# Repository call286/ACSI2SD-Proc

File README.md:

# ACSI2SD-Proc
version for QFP100 controller
ACSI0123_512M.xml contains default configuration for scsi2sd-util

# Hardware - finally with placement help and board layout

- Board layout isn't the original layout, it's just for helping with rough position of parts
- DRC/ERC passing
- interactive BOM in kicad folder

Board Render Front           |  Board Render Back
:-------------------------:|:-------------------------:
 |

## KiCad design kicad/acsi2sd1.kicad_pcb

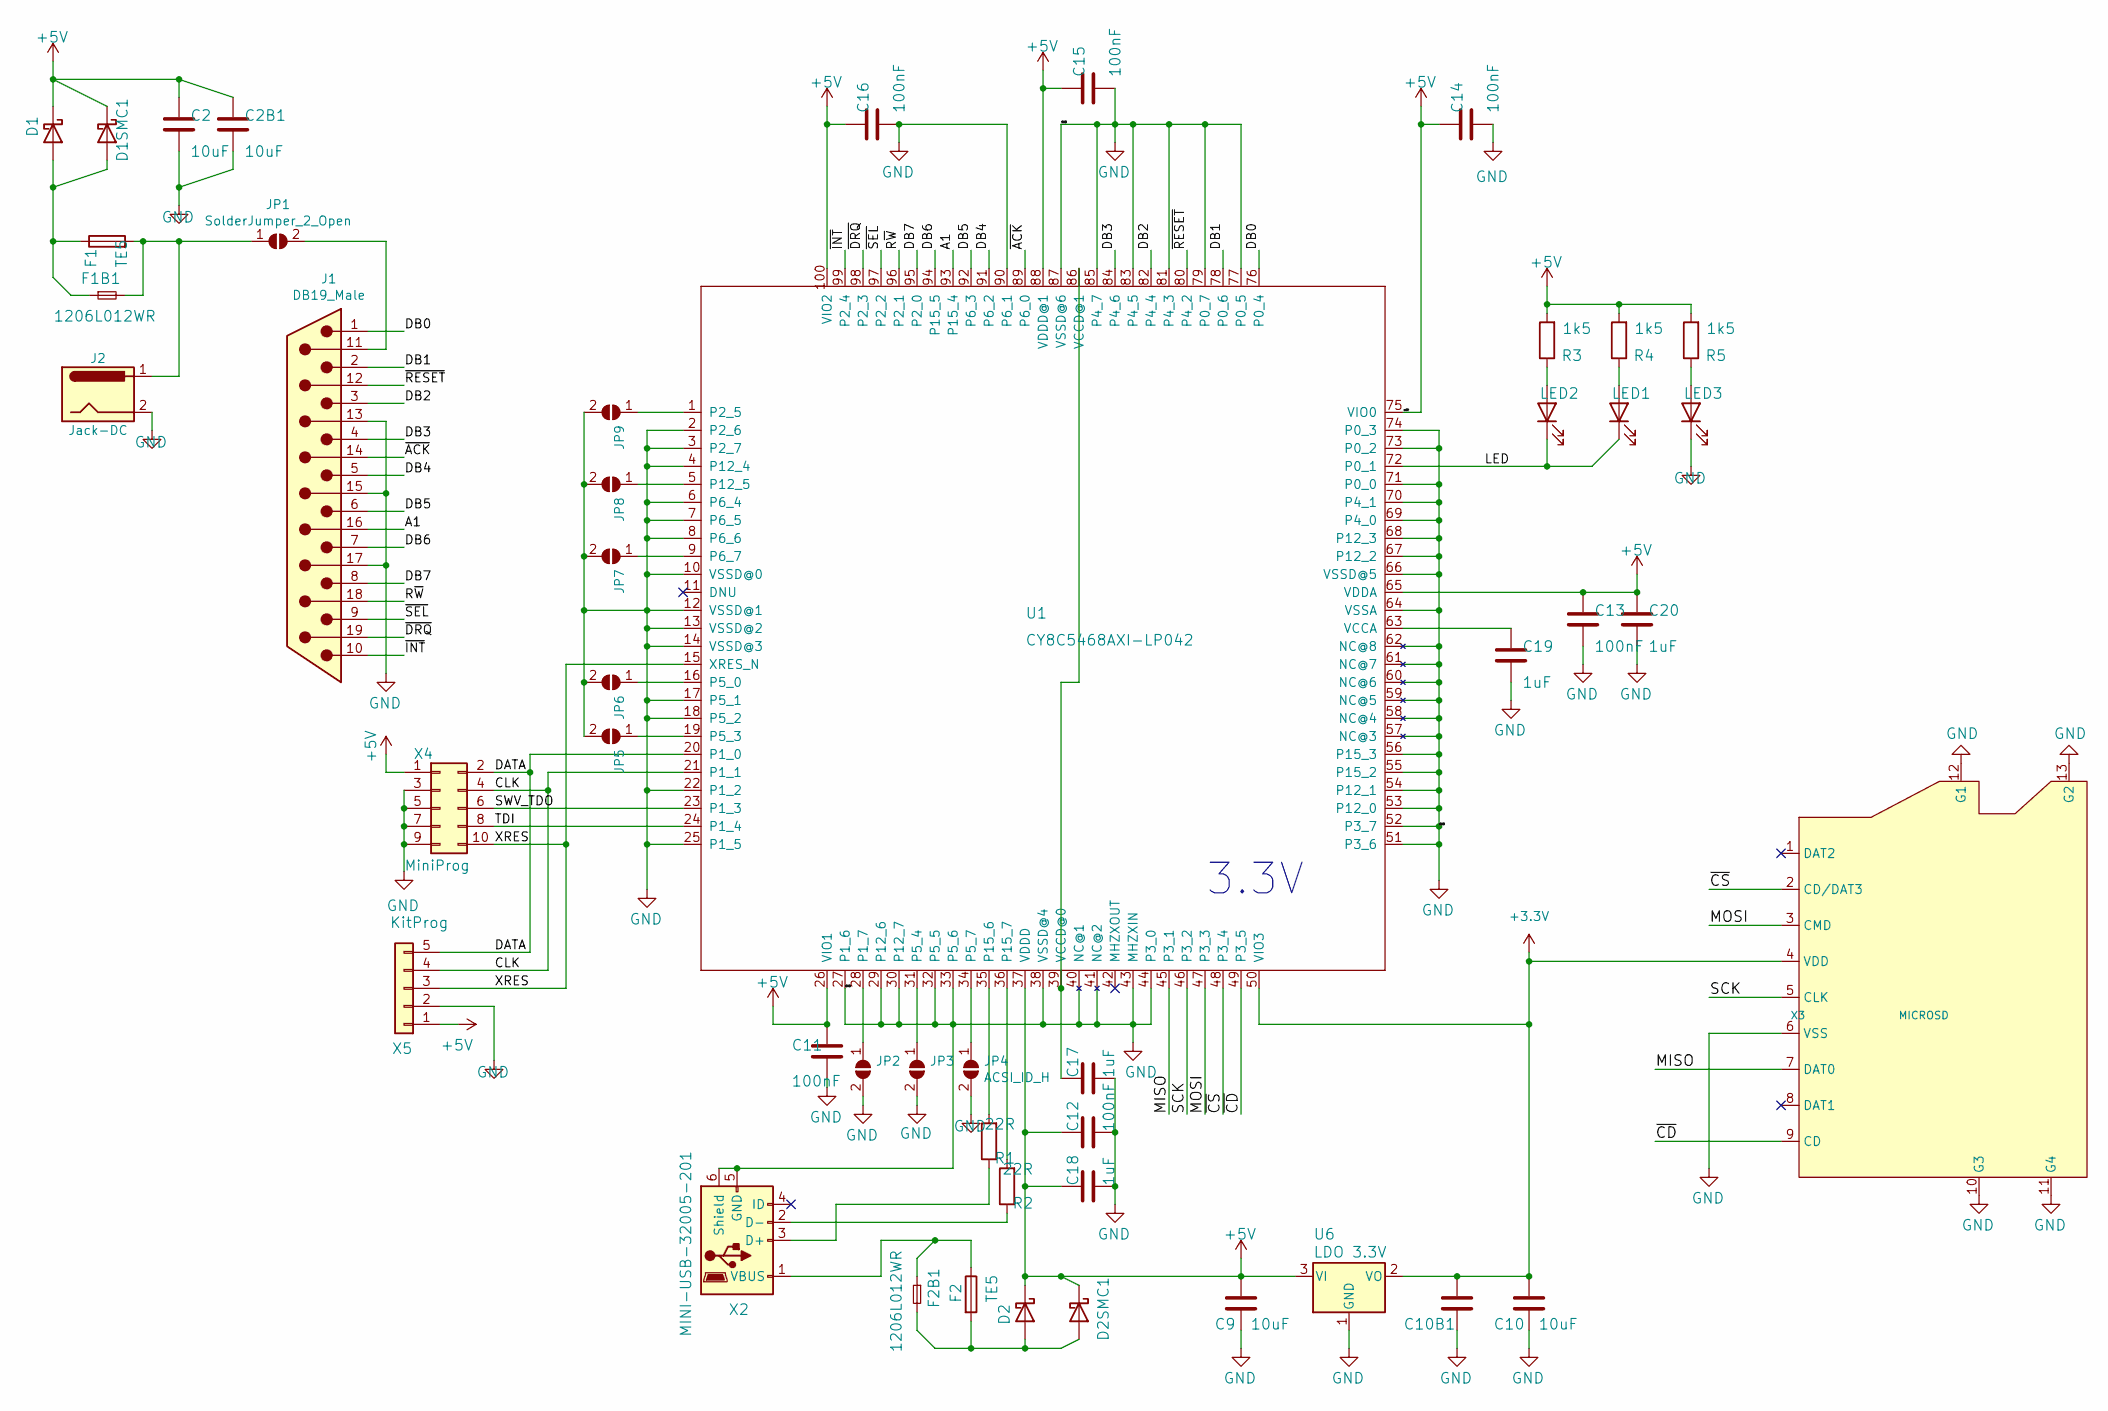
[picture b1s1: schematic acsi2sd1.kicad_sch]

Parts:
C2, C9, C10: 10uF; C_0805_2012Metric_Pad1.18x1.45mm_HandSolder
C2B1, C10B1: 10uF; C_1206_3216Metric_Pad1.33x1.80mm_HandSolder
C11, C12, C13, C14, C15, C16: 100nF; C_0805_2012Metric_Pad1.18x1.45mm_HandSolder
C17, C18, C19, C20: 1uF; C_0805_2012Metric_Pad1.18x1.45mm_HandSolder
D1, D2: SCHOTTKY-DIODEDO214AC; D_SMA_Handsoldering
D1SMC1, D2SMC1: SCHOTTKY-DIODESMC; D_SMC_Handsoldering
F1, F2: TE5; Fuse_Littelfuse_395Series
F1B1, F2B1: 1206L012WR; Fuse_1206_3216Metric_Pad1.42x1.75mm_HandSolder
J1: DB19_Male; DSUB-19_Male_Vertical_MountingHoles
J2: Jack-DC; BarrelJack_Horizontal
JP1, JP2, JP3, JP5, JP6, JP7, JP8, JP9: SolderJumper_2_Open; SolderJumper-2_P1.3mm_Open_Pad1.0x1.5mm
JP4: ACSI_ID_H; SolderJumper-2_P1.3mm_Open_Pad1.0x1.5mm
LED1: LEDCHIPLED_0805; LED_0805_2012Metric_Pad1.15x1.40mm_HandSolder
LED2: SD active; LED_0805_2012Metric_Pad1.15x1.40mm_HandSolder
LED3: Power; LED_0805_2012Metric_Pad1.15x1.40mm_HandSolder
R1, R2: 22R; R_0805_2012Metric_Pad1.20x1.40mm_HandSolder
R3, R4, R5: 1k5; R_0805_2012Metric_Pad1.20x1.40mm_HandSolder
U1: CY8C5468AXI-LP042; TQFP-100_14x14mm_P0.5mm
U6: LDO 3.3V; TO-252-3_TabPin2
X2: MINI-USB-32005-201; USB_Mini-B_Wuerth_65100516121_Horizontal
X3: MICROSD; lcsc_c111196_microsd_slot; LCSC Part C111196
X4: MiniProg; PinHeader_2x05_P2.54mm_Vertical_SMD
X5: KitProg; PinHeader_1x05_P2.54mm_Vertical

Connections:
+3.3V: C10.1, C10B1.1, U1.50 (VIO3), U6.2 (VO), X3.4 (VDD)
+5V: C2.1, C2B1.1, C9.1, C11.1, C12.1, C13.1, C14.1, C15.1, C16.1, C18.1, C20.1, D1.1 (K), D1SMC1.1 (K), D2.1 (K), D2SMC1.1 (K), R3.2, R4.2, R5.2, U1.26 (VIO1), U1.37 (VDDD), U1.65 (VDDA), U1.75 (VIO0), U1.88 (VDDD@1), U1.100 (VIO2), U6.3 (VI), X4.1, X5.1
/A1: J1.16, U1.93 (P15_4)
/CLK: U1.21 (P1_1), X4.4, X5.4
/DATA: U1.20 (P1_0), X4.2, X5.5
/DB0: J1.1, U1.76 (P0_4)
/DB1: J1.2, U1.78 (P0_6)
/DB2: J1.3, U1.82 (P4_4)
/DB3: J1.4, U1.84 (P4_6)
/DB4: J1.5, U1.91 (P6_2)
/DB5: J1.6, U1.92 (P6_3)
/DB6: J1.7, U1.94 (P15_5)
/DB7: J1.8, U1.95 (P2_0)
/LED: LED1.1 (K), LED2.1 (K), U1.72 (P0_1)
/MISO: U1.45 (P3_1), X3.7 (DAT0)
/MOSI: U1.47 (P3_3), X3.3 (CMD)
/R~W: J1.18, U1.96 (P2_1)
/SCK: U1.46 (P3_2), X3.5 (CLK)
/SWV_TDO: U1.23 (P1_3), X4.6
/TDI: U1.24 (P1_4), X4.8
/XRES: U1.15 (XRES_N), X4.10, X5.3
/~ACK: J1.14, U1.89 (P6_0)
/~CD: U1.49 (P3_5), X3.9 (CD)
/~CS: U1.48 (P3_4), X3.2 (CD/DAT3)
/~DRQ: J1.19, U1.98 (P2_3)
/~INT: J1.10, U1.99 (P2_4)
/~RESET: J1.12, U1.80 (P4_2)
/~SEL: J1.9, U1.97 (P2_2)
GND: C2.2, C2B1.2, C9.2, C10.2, C10B1.2, C11.2, C12.2, C13.2, C14.2, C15.2, C16.2, C17.2, C18.2, C19.2, C20.2, J1.13, J1.15, J1.17, J2.2, JP2.2 (B), JP3.2 (B), JP4.2 (B), JP5.2 (B), JP6.2 (B), JP7.2 (B), JP8.2 (B), JP9.2 (B), LED3.1 (K), U1.2 (P2_6), U1.3 (P2_7), U1.4 (P12_4), U1.6 (P6_4), U1.7 (P6_5), U1.8 (P6_6), U1.10 (VSSD@0), U1.12 (VSSD@1), U1.13 (VSSD@2), U1.14 (VSSD@3), U1.17 (P5_1), U1.18 (P5_2), U1.22 (P1_2), U1.25 (P1_5), U1.27 (P1_6), U1.29 (P12_6), U1.30 (P12_7), U1.32 (P5_5), U1.33 (P5_6), U1.38 (VSSD@4), U1.40 (NC@1), U1.41 (NC@2), U1.43 (MHZXIN), U1.44 (P3_0), U1.51 (P3_6), U1.52 (P3_7), U1.53 (P12_0), U1.54 (P12_1), U1.55 (P15_2), U1.56 (P15_3), U1.57 (NC@3), U1.58 (NC@4), U1.59 (NC@5), U1.60 (NC@6), U1.61 (NC@7), U1.62 (NC@8), U1.64 (VSSA), U1.66 (VSSD@5), U1.67 (P12_2), U1.68 (P12_3), U1.69 (P4_0), U1.70 (P4_1), U1.71 (P0_0), U1.73 (P0_2), U1.74 (P0_3), U1.77 (P0_5), U1.79 (P0_7), U1.81 (P4_3), U1.83 (P4_5), U1.85 (P4_7), U1.87 (VSSD@6), U1.90 (P6_1), U6.1 (GND), X2.5 (GND), X2.6 (Shield), X3.6 (VSS), X3.10 (G3), X3.11 (G4), X3.12 (G1), X3.13 (G2), X4.3, X4.5, X4.7, X4.9, X5.2
unnamed: C17.1, U1.39 (VCCD@0), U1.86 (VCCD@1)
unnamed: C19.1, U1.63 (VCCA)
unnamed: D1.2 (A), D1SMC1.2 (A), F1.1, F1B1.1
unnamed: D2.2 (A), D2SMC1.2 (A), F2.2, F2B1.2
unnamed: F1.2, F1B1.2, J2.1, JP1.1 (A)
unnamed: F2.1, F2B1.1, X2.1 (VBUS)
unnamed: J1.11, JP1.2 (B)
unnamed: JP2.1 (A), U1.28 (P1_7)
unnamed: JP3.1 (A), U1.31 (P5_4)
unnamed: JP4.1 (A), U1.34 (P5_7)
unnamed: JP5.1 (A), U1.19 (P5_3)
unnamed: JP6.1 (A), U1.16 (P5_0)
unnamed: JP7.1 (A), U1.9 (P6_7)
unnamed: JP8.1 (A), U1.5 (P12_5)
unnamed: JP9.1 (A), U1.1 (P2_5)
unnamed: LED1.2 (A), R4.1
unnamed: LED2.2 (A), R3.1
unnamed: LED3.2 (A), R5.1
unnamed: R1.1, X2.3 (D+)
unnamed: R1.2, U1.35 (P15_6)
unnamed: R2.1, X2.2 (D-)
unnamed: R2.2, U1.36 (P15_7)

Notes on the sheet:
3.3V

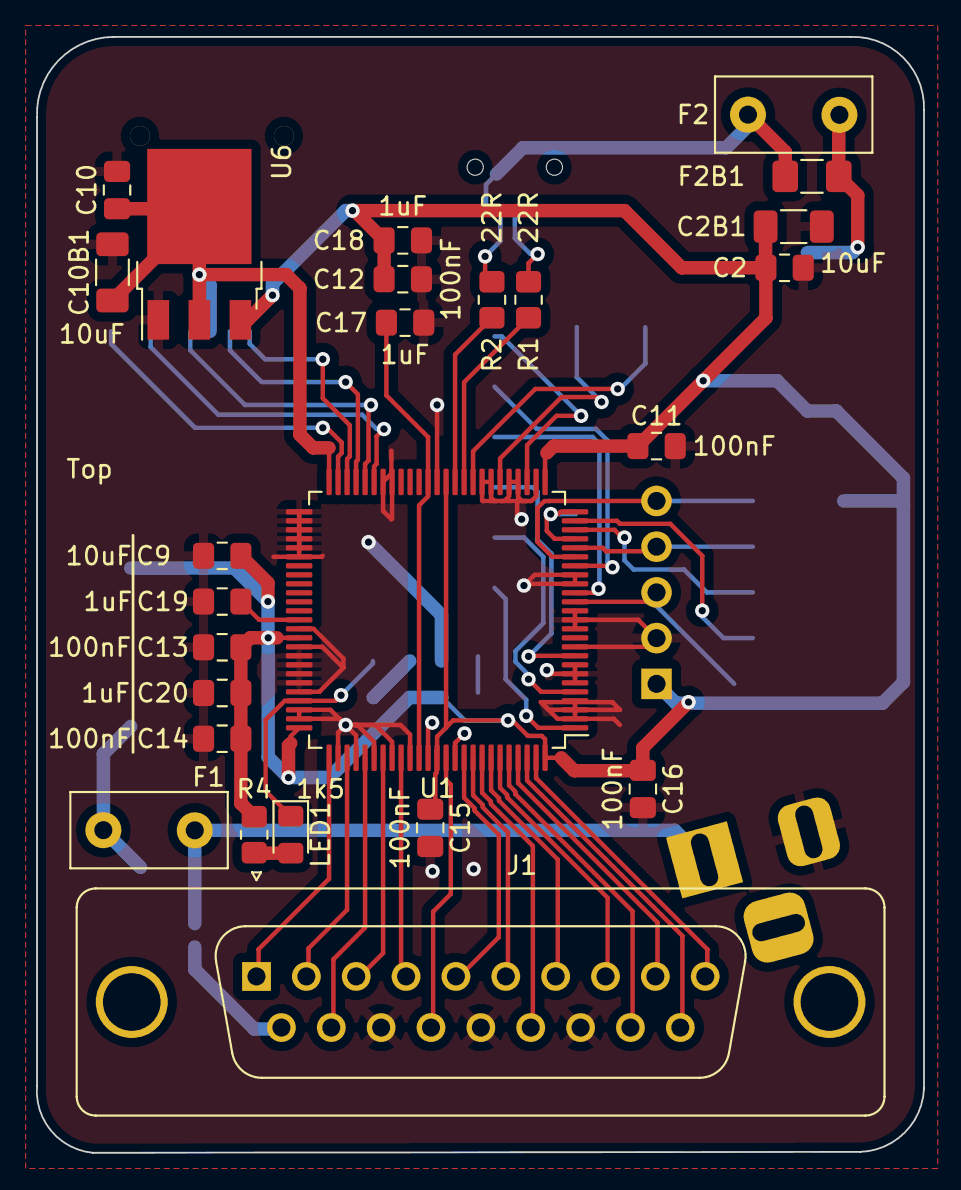
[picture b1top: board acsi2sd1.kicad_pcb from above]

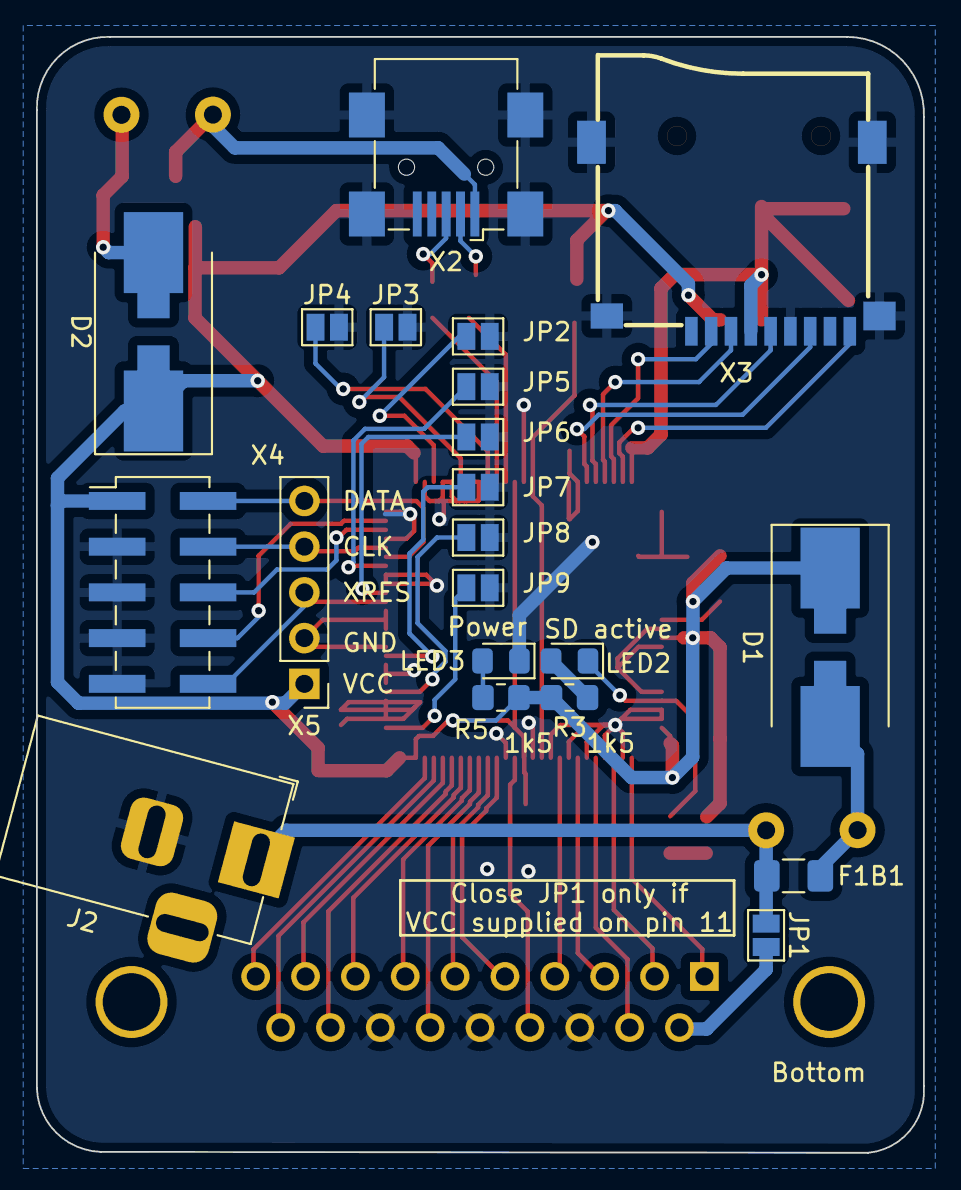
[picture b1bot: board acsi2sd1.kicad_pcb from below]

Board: 2 copper layers, 49.3 x 62.0 mm, 48 parts (23 on the bottom side), 51 nets.

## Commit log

2022-07-19 Moved to KiCAD 6, added board layout and interactive BOM
